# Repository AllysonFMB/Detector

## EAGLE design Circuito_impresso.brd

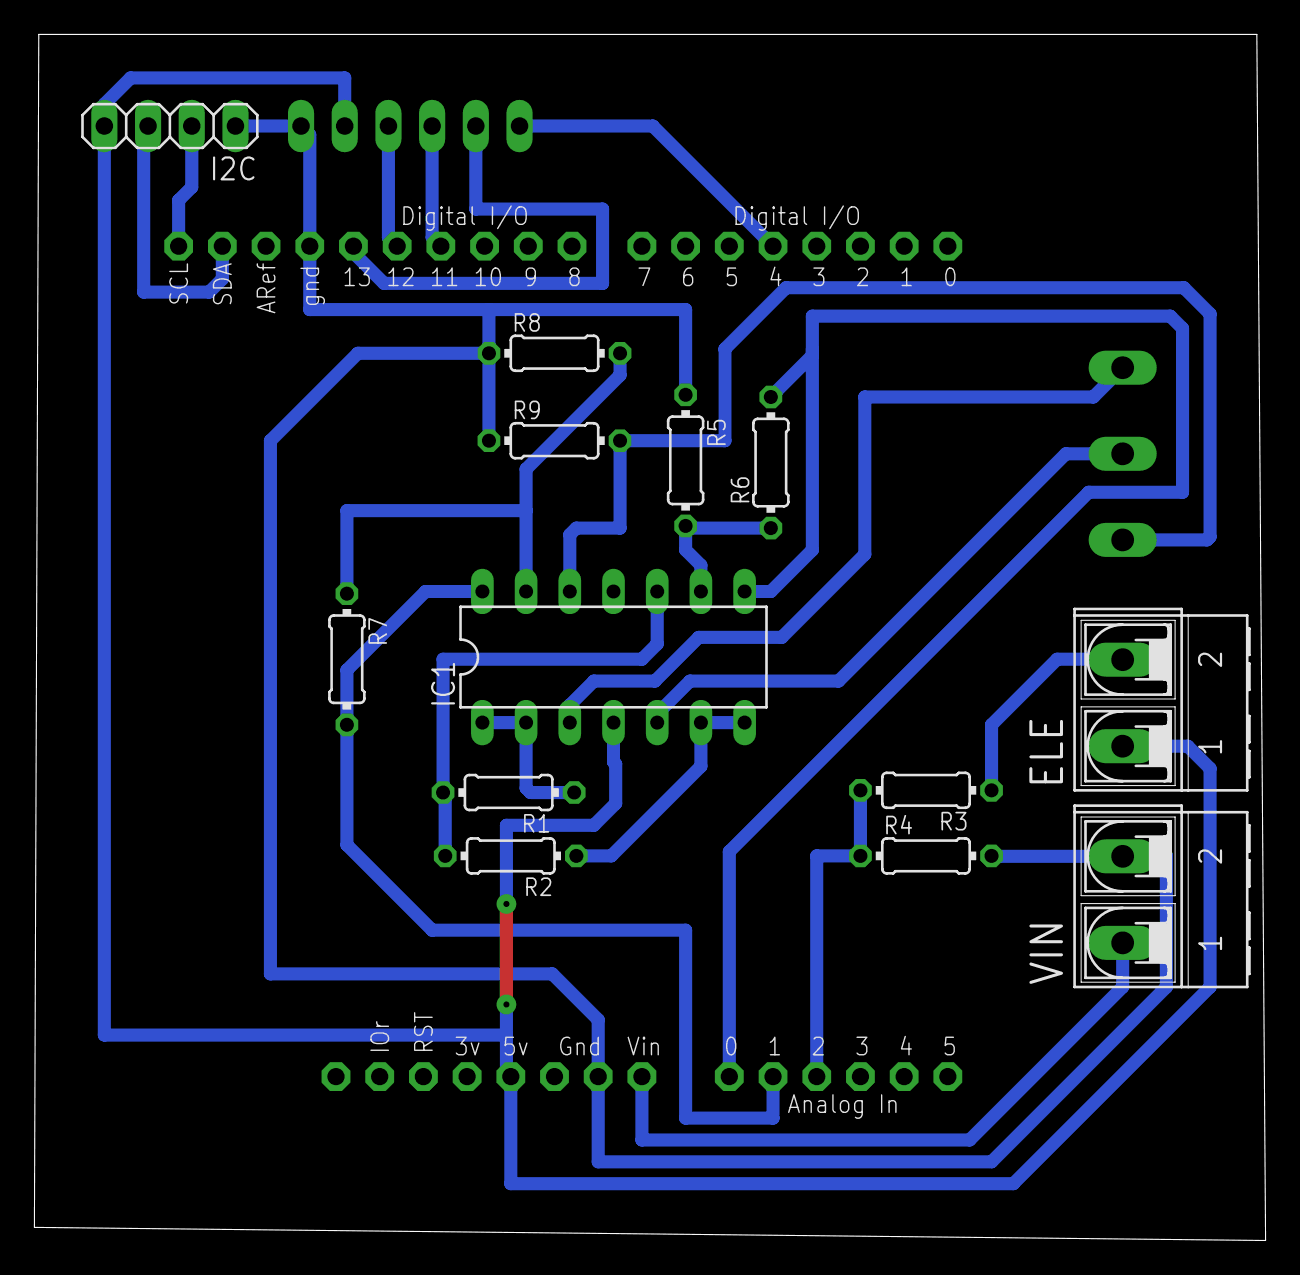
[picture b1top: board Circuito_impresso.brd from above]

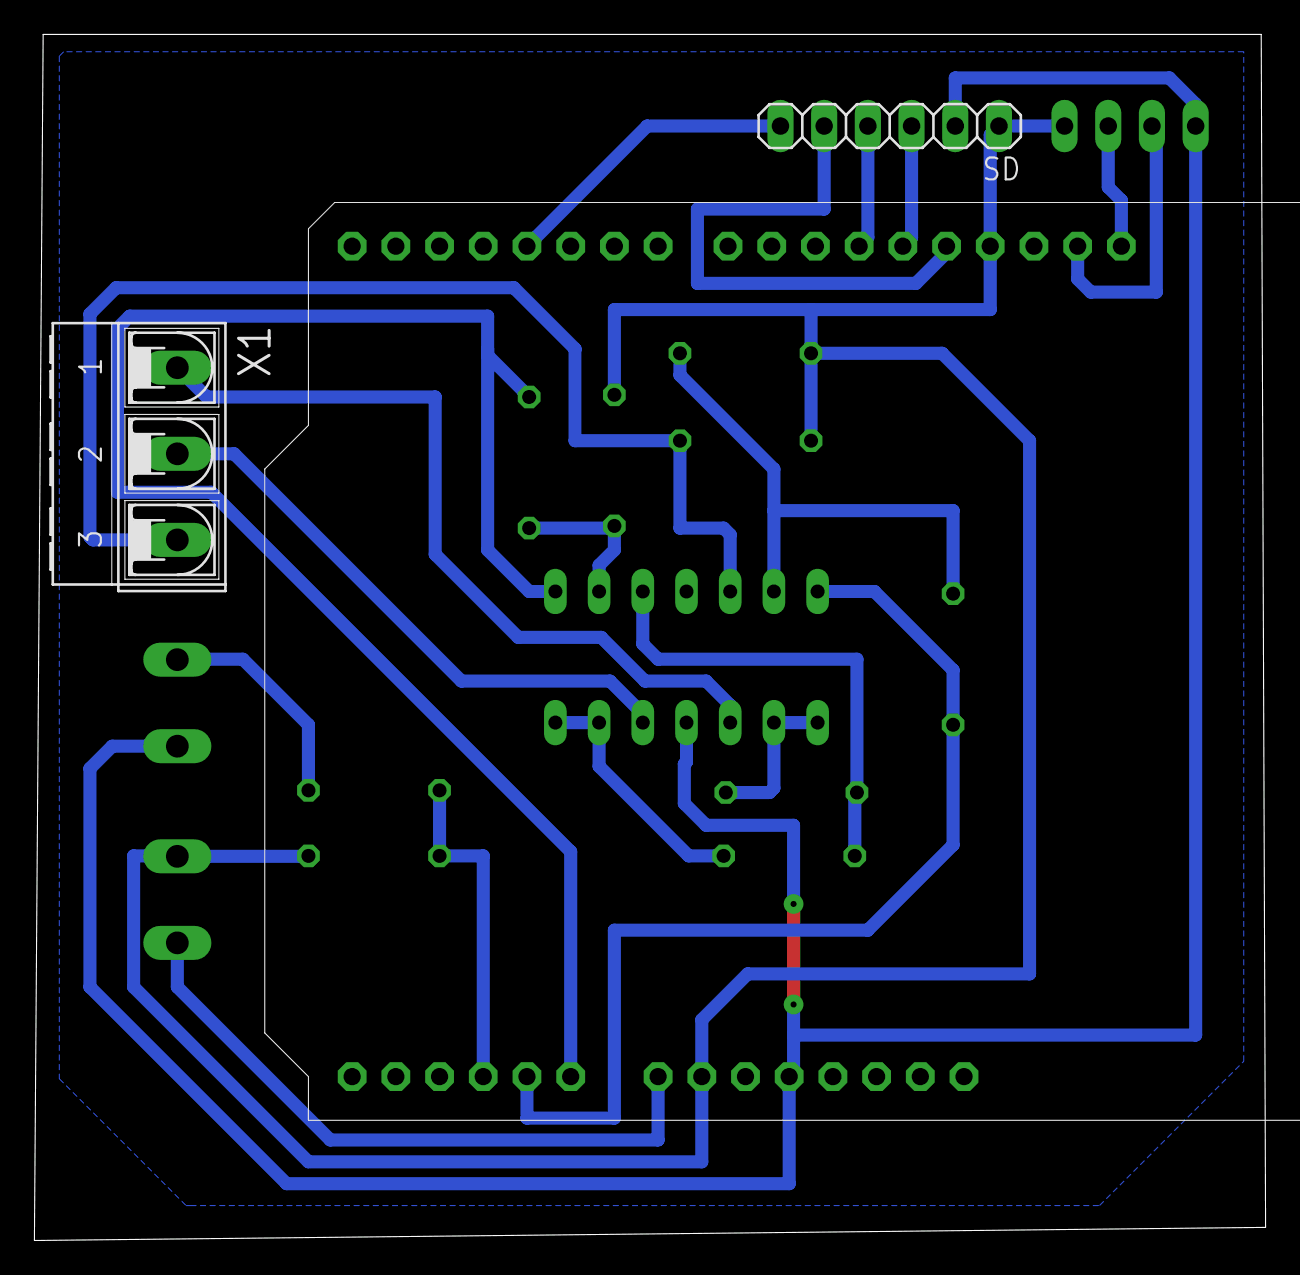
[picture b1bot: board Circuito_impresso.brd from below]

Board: 2 copper layers, 71.6 x 70.1 mm, 16 parts (2 on the bottom side), 21 nets.

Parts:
ELE: AK500/2-H
I2C: 1X04
IC1: LM324N; DIL14
R1, R2, R4, R5, R6, R8: 10K; 0204/7
R3: 1K; 0204/7
R7: 2K; 0204/7
R9: 1; 0204/7
SD: 1X06
U1: ARDUINOR3-BPLACE
VIN: AK500/2-H
X1: AK500/3-H

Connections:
A1: IC1.8, R6.2, U1.A0
GND: I2C.1, IC1.11, R4.2, R5.1, R8.1, R9.1, SD.1, U1.GND, U1.GND1, VIN.2
unnamed: I2C.3, U1.SDA
unnamed: IC1.1, IC1.2, R1.1
unnamed: IC1.3, X1.1
unnamed: ELE.2, R3.1
unnamed: IC1.6, IC1.7, R2.1
unnamed: I2C.2, U1.SCL
unnamed: IC1.5, X1.2
unnamed: IC1.9, R5.2, R6.1
unnamed: IC1.10, R1.2, R2.2
unnamed: U1.VIN, VIN.1
unnamed: SD.5, U1.D13
unnamed: SD.3, U1.D12
unnamed: SD.4, U1.D11
unnamed: SD.6, U1.D4
unnamed: IC1.13, R7.1, R8.2
unnamed: ELE.1, I2C.4, IC1.4, SD.2, U1.5V
unnamed: IC1.12, R9.2, X1.3
unnamed: IC1.14, R7.2, U1.A1
unnamed: R3.2, R4.1, U1.A2

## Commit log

2020-12-21 Detector de solução aquosa
2020-12-21 Create REFERÊNCIA
2020-12-21 Anexo
